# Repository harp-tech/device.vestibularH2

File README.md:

## Harp FastStepper

This repository contains the device metadata, firmware and high-level interface to the FastStepper device. Below are simple getting started instructions for maintainers to create a new device using the automatic code generators.

### Device metadata

#### Prerequisites

1. Install [Visual Studio Code](https://code.visualstudio.com/)
2. Install the [YAML](https://marketplace.visualstudio.com/items?itemName=redhat.vscode-yaml) extension.

The `device.yml` file in the root of the project contains the FastStepper device metadata. A complete specification of device registers, including any bit masks, group masks, and payload specs needs to be provided for code generation to work.

### Generating interface and firmware

#### Prerequisites

1. Install [`dotnet`](https://dotnet.microsoft.com/)
2. Install `dotnet-t4`
```
dotnet tool install -g dotnet-t4
```

The `Generators` folder contains all text templates and project files required to generate both the firmware headers and the interface for the FastStepper device. To run the text templating engine just build the project inside this folder.

```
cd Generators
dotnet build
```

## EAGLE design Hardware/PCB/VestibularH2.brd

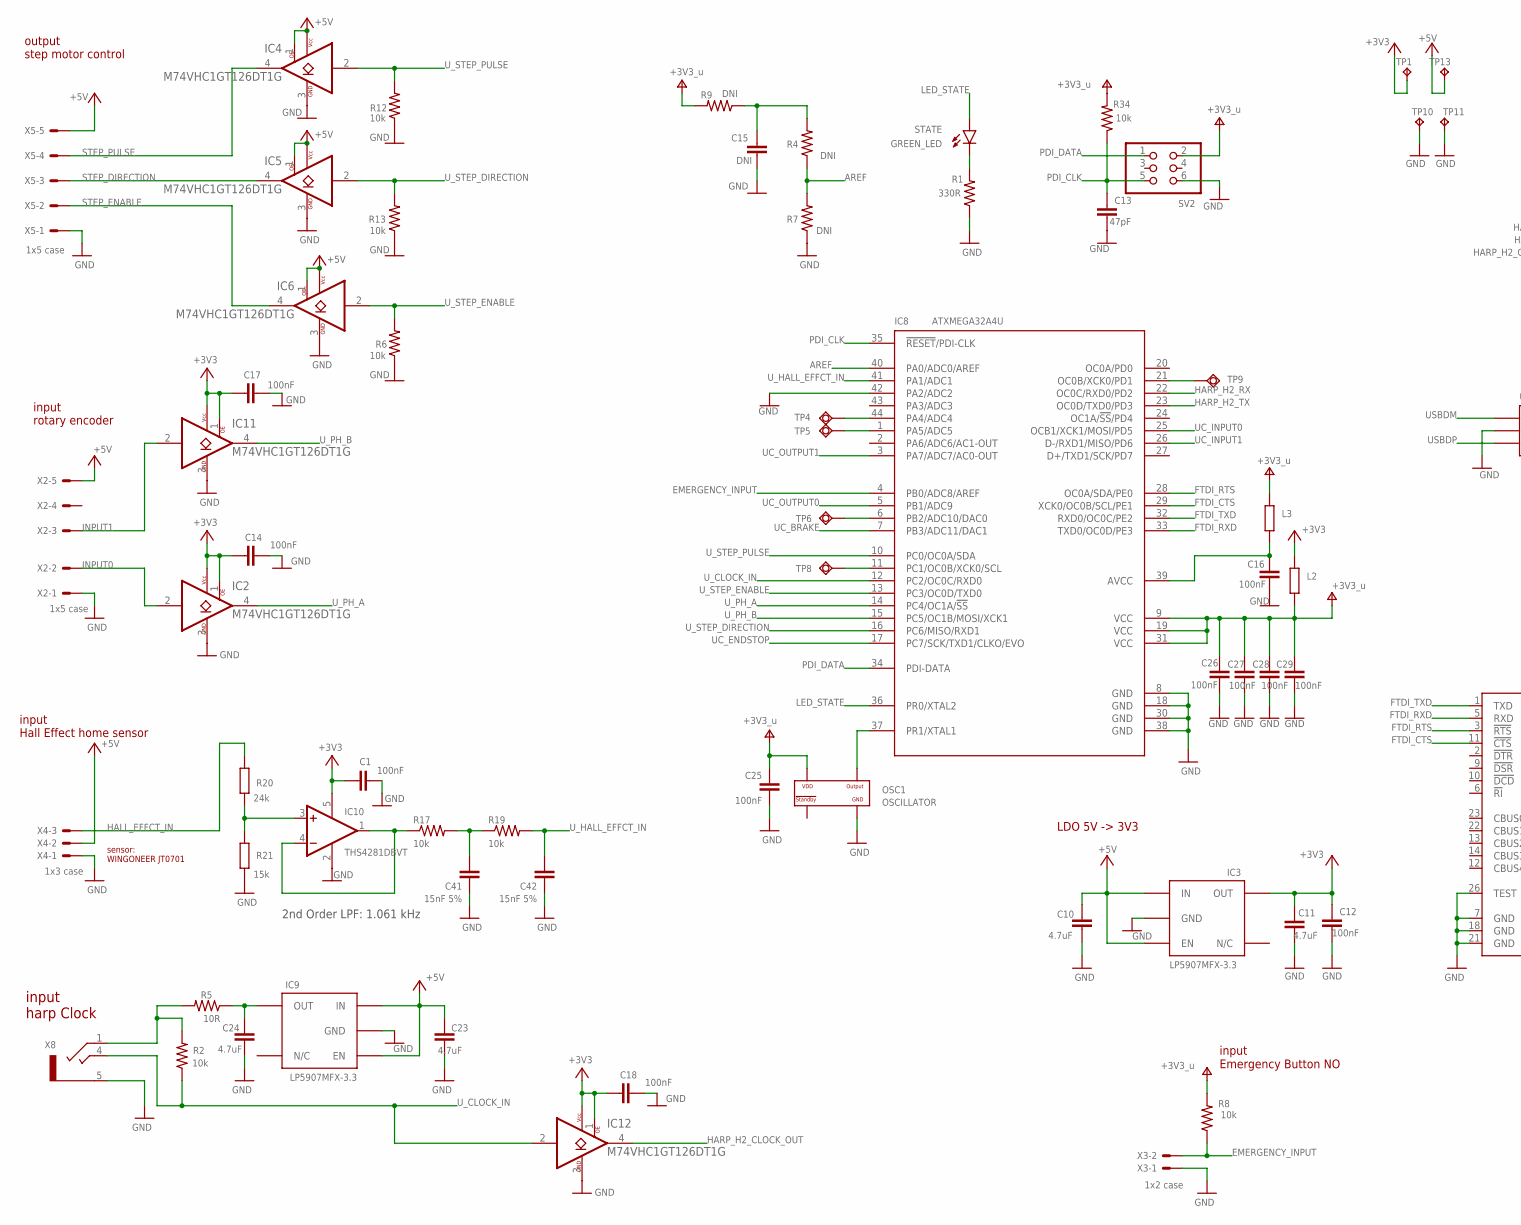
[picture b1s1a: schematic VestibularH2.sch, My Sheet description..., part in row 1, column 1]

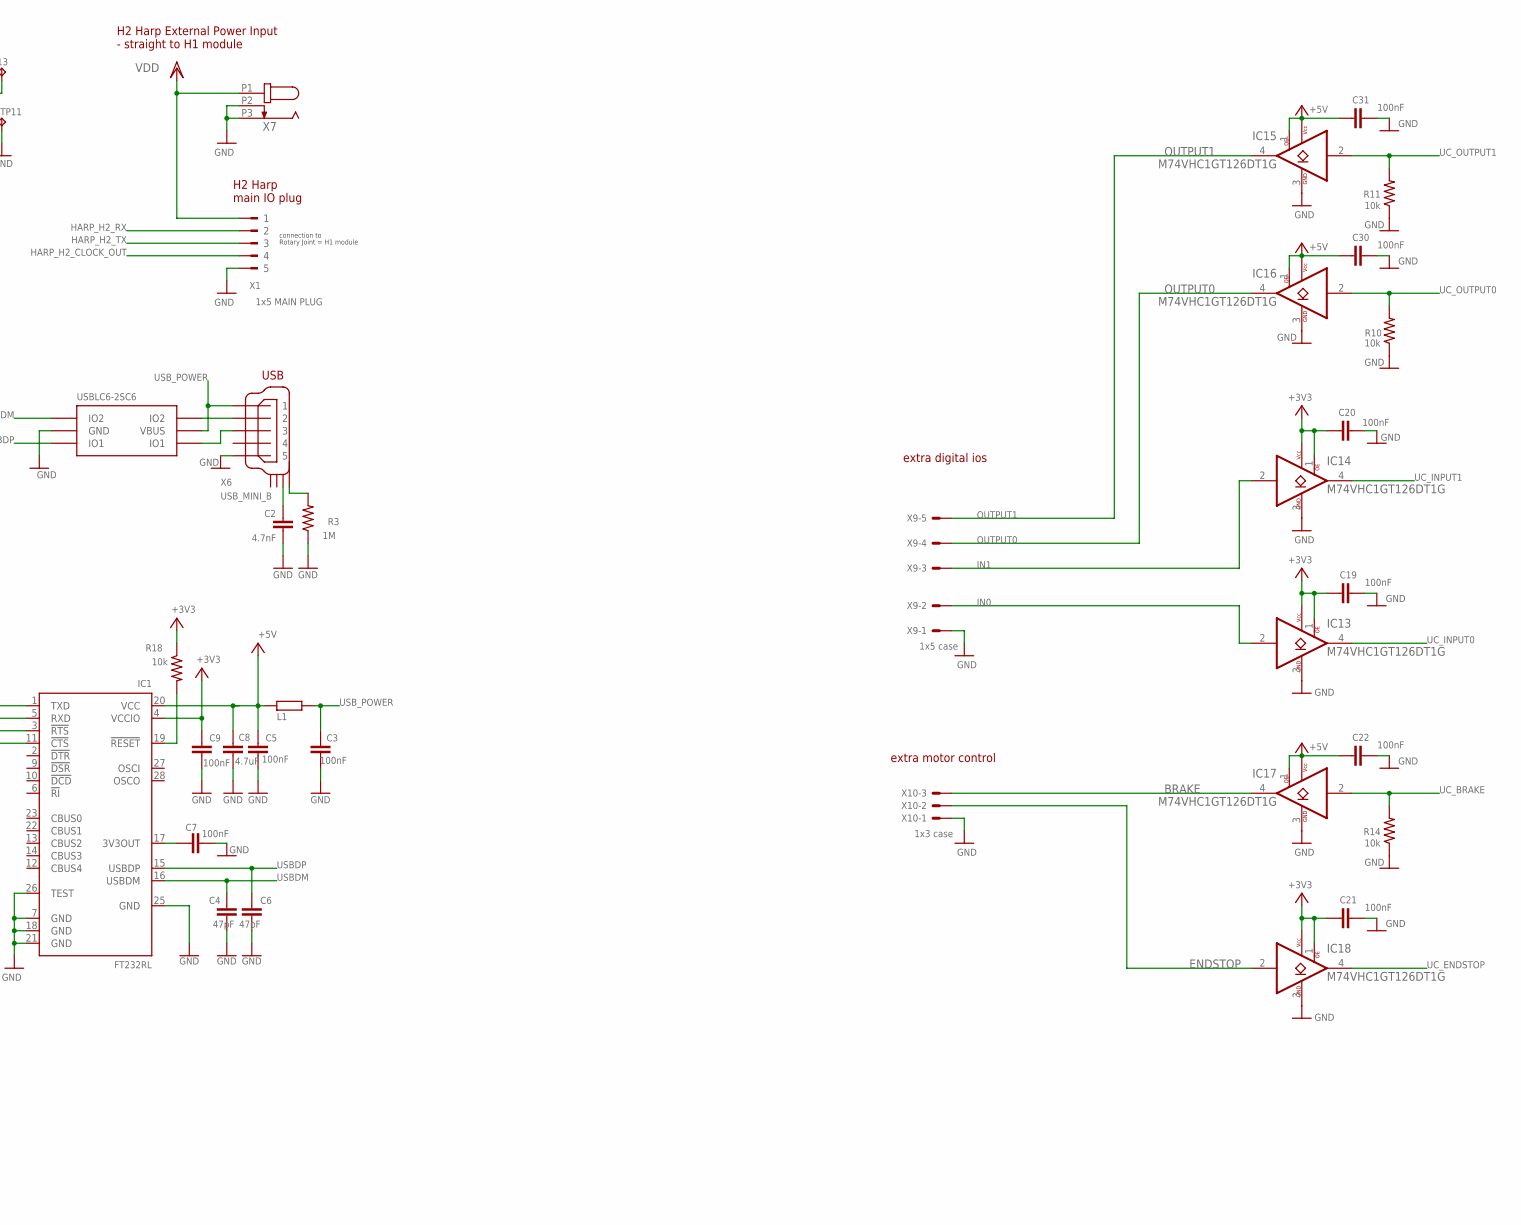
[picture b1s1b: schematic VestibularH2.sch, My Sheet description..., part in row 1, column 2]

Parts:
C1, C3, C5, C7, C9, C12, C14, C16, C17, C18, C19, C20, C21, C22, C25, C26, C27, C28, C29, C30, C31: 100nF; C0402K; MPN C1005X7R1H104K050BB
C2: 4.7nF; C0402K; MPN CC0402KRX7R8BB472
C4, C6, C13: 47pF; C0402K; MPN 04025A470JAT2A
C8, C10, C11, C23, C24: 4.7uF; C0603K; MPN C1608X6S1C475K080AC
C15: DNI; C0603K; MPN DNI
C41, C42: 15nF 5%; C0402K; MPN CGA2B3X7R1V153K050BB
IC1: FT232RL; SSOP28; MPN FT232RL
IC2, IC4, IC5, IC6, IC11, IC12, IC13, IC14, IC15, IC16, IC17, IC18: M74VHC1GT126DT1G; TSOP-5; MPN M74VHC1GT126DT1G; DIGIKEY_PN M74VHC1GT126DT1GOSDKR-ND
IC3, IC9: LP5907MFX-3.3; TSOT23-5; MPN LP5907MFX-3.3/NOPB
IC7: USBLC6-2SC6; SOT23-6L; MPN USBLC6-2SC6
IC8: ATXMEGA32A4U; TQFP44; MPN ATXMEGA32A4U-AUR
IC10: THS4281DBVT; SOT23-5; MPN THS4281DBVT
L1, L2, L3: 40R@100MHz; R0805; MPN MI0805K400R-10
OSC1: OSCILLATOR; OSCILLATOR_3.2X2.5; MPN DSC1001CI5-032.0000
R1: 330R; R0402; MPN RC0402FR-07330RL
R2, R6, R8, R10, R11, R12, R13, R14, R17, R18, R19, R34: 10k; R0402; MPN CRCW040210K0FKED
R3: 1M; R0402; MPN CRCW04021M00FKED
R4, R7, R9: DNI; R0402; MPN DNI
R5: 10R; R0402; MPN ERJ-PA2J100X
R20: 24k; R0402; MPN ERJ-2RKF2402X
R21: 15k; R0402; MPN ERJ-2RKF1502X
STATE: GREEN_LED; CHIP-LED0603; MPN LTST-C191KGKT
SV2: PINHD-2X3; 2X03; MPN 609-3210-ND
TP1, TP10, TP11, TP13: NO_COMPONENT; B1,27
TP4, TP5, TP6, TP8, TP9: NO_COMPONENT; TP11R
X1: 1x5 MAIN PLUG; 90G-5; MPN 20.155MH/5-E
X2, X5, X9: 1x5 case; 22-23-2051; MPN 282834-5
X3: 1x2 case; 22-23-2021; MPN 282834-2
X4, X10: 1x3 case; 22-23-2031; MPN 282834-3
X6: USB_MINI_B; 240-0002-1; MPN UX60-MB-5S8
X7: DC_JACK2.1MM; DC_POWER_INPUT_2.1MM; MPN 163-179PH-EX
X8: CLCK_JACK; 35RASMT2BHNTRX; MPN 35RASMT2BHNTRX

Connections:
+3V3: C1.1, C9.1, C11.1, C12.1, C14.1, C17.1, C18.1, C19.1, C20.1, C21.1, IC1.4 (VCCIO), IC2.1 (OE), IC2.5 (VCC), IC3.5 (OUT), IC10.5 (V+), IC11.1 (OE), IC11.5 (VCC), IC12.1 (OE), IC12.5 (VCC), IC13.1 (OE), IC13.5 (VCC), IC14.1 (OE), IC14.5 (VCC), IC18.1 (OE), IC18.5 (VCC), L2.2, R18.1, TP1.TP
+5V: C5.1, C8.1, C10.1, C22.1, C23.1, C30.1, C31.1, IC1.20 (VCC), IC3.1 (IN), IC3.3 (EN), IC4.1 (OE), IC4.5 (VCC), IC5.1 (OE), IC5.5 (VCC), IC6.1 (OE), IC6.5 (VCC), IC9.1 (IN), IC9.3 (EN), IC15.1 (OE), IC15.5 (VCC), IC16.1 (OE), IC16.5 (VCC), IC17.1 (OE), IC17.5 (VCC), L1.1, TP13.TP, X2.5, X4.2, X5.5
AREF: IC8.40 (PA0/ADC0/AREF), R4.1, R7.2
BRAKE: IC17.4 (Y), X10.3
EMERGENCY_INPUT: IC8.4 (PB0/ADC8/AREF), R8.1, X3.2
ENDSTOP: IC18.2 (A), X10.2
FTDI_CTS: IC1.11 (!CTS), IC8.29 (XCK0/OC0B/SCL/PE1)
FTDI_RTS: IC1.3 (!RTS), IC8.28 (OC0A/SDA/PE0)
FTDI_RXD: IC1.5 (RXD), IC8.33 (TXD0/OC0D/PE3)
FTDI_TXD: IC1.1 (TXD), IC8.32 (RXD0/OC0C/PE2)
GND: C1.2, C2.2, C3.2, C4.2, C5.2, C6.2, C7.2, C8.2, C9.2, C10.2, C11.2, C12.2, C13.2, C14.2, C15.2, C16.2, C17.2, C18.2, C19.2, C20.2, C21.2, C22.2, C23.2, C24.2, C25.2, C26.2, C27.2, C28.2, C29.2, C30.2, C31.2, C41.1, C42.1, IC1.7 (GND), IC1.18 (GND), IC1.21 (GND), IC1.25 (GND), IC1.26 (TEST), IC2.3 (GND), IC3.2 (GND), IC4.3 (GND), IC5.3 (GND), IC6.3 (GND), IC7.P$2 (GND), IC8.8 (GND), IC8.18 (GND), IC8.30 (GND), IC8.38 (GND), IC8.42 (PA2/ADC2), IC9.2 (GND), IC10.2 (V-), IC11.3 (GND), IC12.3 (GND), IC13.3 (GND), IC14.3 (GND), IC15.3 (GND), IC16.3 (GND), IC17.3 (GND), IC18.3 (GND), OSC1.P$2 (GND), R1.1, R3.1, R6.1, R7.1, R10.1, R11.1, R12.1, R13.1, R14.1, R21.1, SV2.6, TP10.TP, TP11.TP, X1.5, X2.1, X3.1, X4.1, X5.1, X6.P$5 (5), X7.P2 (2), X7.P3 (3), X8.5, X9.1, X10.1
HALL_EFFCT_IN: R20.2, X4.3
HARP_H2_CLOCK_OUT: IC12.4 (Y), X1.4
HARP_H2_RX: IC8.22 (OC0C/RXD0/PD2), X1.2
HARP_H2_TX: IC8.23 (OC0D/TXD0/PD3), X1.3
IN0: IC13.2 (A), X9.2
IN1: IC14.2 (A), X9.3
INPUT0: IC2.2 (A), X2.2
INPUT1: IC11.2 (A), X2.3
LED_STATE: IC8.36 (PR0/XTAL2), STATE.A
unnamed: R3.2, X6.SHIELD_4
unnamed: IC7.P$4 (IO2), X6.P$2 (2)
unnamed: IC7.P$6 (IO1), X6.P$3 (3)
unnamed: R1.2, STATE.C
unnamed: IC8.44 (PA4/ADC4), TP4.TP
unnamed: IC8.1 (PA5/ADC5), TP5.TP
unnamed: IC8.6 (PB2/ADC10/DAC0), TP6.TP
unnamed: C2.1, X6.SHIELD_3
unnamed: IC8.11 (PC1/OC0B/XCK0/SCL), TP8.TP
unnamed: IC8.21 (OC0B/XCK0/PD1), TP9.TP
unnamed: C7.1, IC1.17 (3V3OUT)
unnamed: C41.2, R17.2, R19.1
unnamed: C15.1, R4.2, R9.1
unnamed: C16.1, IC8.39 (AVCC), L3.1
unnamed: IC10.1 (OUT), IC10.4 (-IN), R17.1
unnamed: IC10.3 (+IN), R20.1, R21.2
unnamed: R2.2, R5.2, X8.1
unnamed: C24.1, IC9.5 (OUT), R5.1
unnamed: IC1.19 (!RESET), R18.2
OSC2: IC8.37 (PR1/XTAL1), OSC1.P$3 (OUTPUT)
OUTPUT0: IC16.4 (Y), X9.4
OUTPUT1: IC15.4 (Y), X9.5
PDI_CLK: C13.1, IC8.35 (!RESET!/PDI-CLK), R34.1, SV2.5
PDI_DATA: IC8.34 (PDI-DATA), SV2.1
STEP_DIRECTION: IC5.4 (Y), X5.3
STEP_ENABLE: IC6.4 (Y), X5.2
STEP_PULSE: IC4.4 (Y), X5.4
UC_BRAKE: IC8.7 (PB3/ADC11/DAC1), IC17.2 (A), R14.2
UC_ENDSTOP: IC8.17 (PC7/SCK/TXD1/CLKO/EVO), IC18.4 (Y)
UC_INPUT0: IC8.25 (OCB1/XCK1/MOSI/PD5), IC13.4 (Y)
UC_INPUT1: IC8.26 (D-/RXD1/MISO/PD6), IC14.4 (Y)
UC_OUTPUT0: IC8.5 (PB1/ADC9), IC16.2 (A), R10.2
UC_OUTPUT1: IC8.3 (PA7/ADC7/AC0-OUT), IC15.2 (A), R11.2
USBDM: C4.1, IC1.16 (USBDM), IC7.P$3 (IO2)
USBDP: C6.1, IC1.15 (USBDP), IC7.P$1 (IO1)
USB_POWER: C3.1, IC7.P$5 (VBUS), L1.2, X6.P$1 (1)
U_CLOCK_IN: IC8.12 (PC2/OC0C/RXD0), IC12.2 (A), R2.1, X8.4
U_HALL_EFFCT_IN: C42.2, IC8.41 (PA1/ADC1), R19.2
U_PH_A: IC2.4 (Y), IC8.14 (PC4/OC1A/!SS)
U_PH_B: IC8.15 (PC5/OC1B/MOSI/XCK1), IC11.4 (Y)
U_STEP_DIRECTION: IC5.2 (A), IC8.16 (PC6/MISO/RXD1), R13.2
U_STEP_ENABLE: IC6.2 (A), IC8.13 (PC3/OC0D/TXD0), R6.2
U_STEP_PULSE: IC4.2 (A), IC8.10 (PC0/OC0A/SDA), R12.2
V+: C25.1, C26.1, C27.1, C28.1, C29.1, IC8.9 (VCC), IC8.19 (VCC), IC8.31 (VCC), L2.1, L3.2, OSC1.P$4 (VDD), R8.2, R9.2, R34.2, SV2.2
VDD: X1.1, X7.P1 (1)

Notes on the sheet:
H2 Harp main IO plug
input rotary encoder
input Hall Effect home sensor
input harp Clock
output step motor control
input Emergency Button NO
USB
sensor: WINGONEER JT0701
H2 Harp External Power Input - straight to H1 module
connection to Rotary Joint = H1 module
2nd Order LPF: 1.061 kHz
LDO 5V -> 3V3
extra digital ios
extra motor control

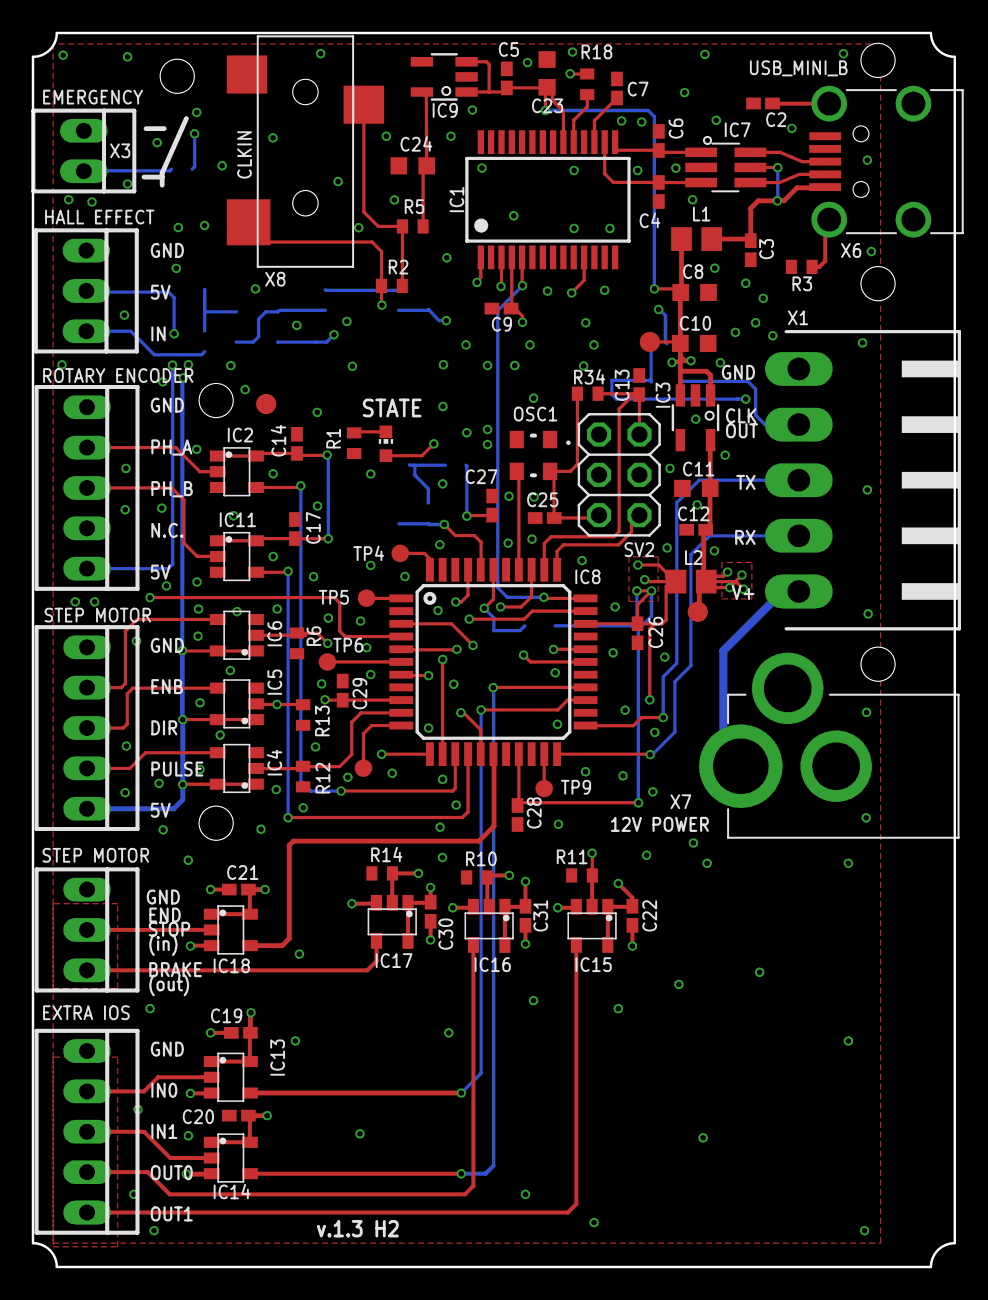
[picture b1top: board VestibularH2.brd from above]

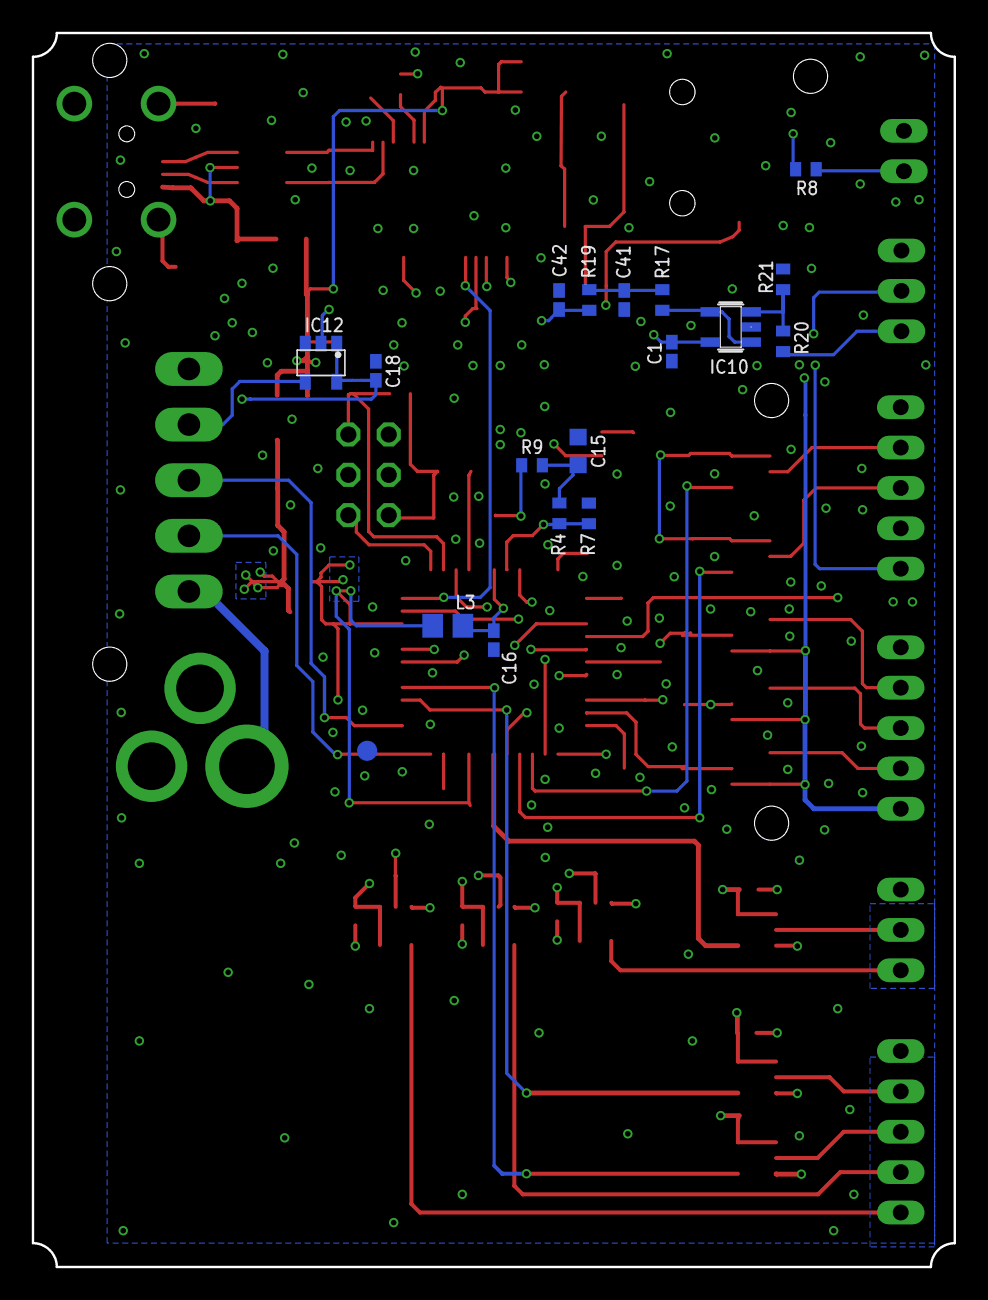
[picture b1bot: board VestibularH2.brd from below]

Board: 4 copper layers, 58.0 x 77.6 mm, 96 parts (18 on the bottom side), 65 nets.

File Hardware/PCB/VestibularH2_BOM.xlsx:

VestibularVR H2-module v1.1
.on board
Qty | Parts | Value | OEPS | MPN | Device | Package | Description
21 | C1, C3, C5, C7, C9, C12, C14, C16, C17, C18, C25, C26, C27, C19, C20, C21, C22,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 | 100nF | OEPS010004 | C1005X7R1H104K050BB | C-EUC0402K | C0402K | CAPACITOR, European symbol
1 | R5 | 10R | OEPS020041 | ERJ-PA2J100X | R-US_R0402 | R0402 | RESISTOR, American symbol
12 | R2, R6, R8, R10, R11, R12, R13, R14, R17, R18, R19, R34 | 10k | OEPS020030 | CRCW040210K0FKED | R-US_R0402 | R0402 | RESISTOR, American symbol
1 | R21 | 15k | OEPS020015 | ERJ-2RKF1502X | R-EU_R0402 | R0402 | RESISTOR, European symbol
2 | C41, C42 | 15nF 5% | OEPS010023 | CGA2B3X7R1V153K050BB | C-EUC0402K | C0402K | CAPACITOR, European symbol
1 | R3 | 1M | OEPS020026 | CRCW04021M00FKED | R-US_R0402 | R0402 | RESISTOR, American symbol
1 | X3 | 1x2 case | OEPS070020 | 282834-2 | 22-23-2021 | 22-23-2021 | .100 (2.54mm) Center Header - 2 Pin"
2 | X4, X10 | 1x3 case | OEPS070035 | 282834-3 | 22-23-2031 | 22-23-2031 | .100 (2.54mm) Center Header - 3 Pin"
1 | X1 | 1x5 MAIN PLUG | OEPS070037 | 20.155MH/5-E | 90G-5 | 90G-5 | WEIDMUELLER CLAMP CONNECTOR
3 | X2, X5, X9 | 1x5 case | OEPS070041 | 282834-5 | 22-23-2051 | 22-23-2051 | .100 (2.54mm) Center Header - 5 Pin"
1 | R20 | 24k | OEPS020048 | ERJ-2RKF2402X | R-EU_R0402 | R0402 | RESISTOR, European symbol
1 | R1 | 330R | OEPS020037 | RC0402FR-07330RL | R-US_R0402 | R0402 | RESISTOR, American symbol
1 | C2 | 4.7nF | OEPS010001 | CC0402KRX7R8BB472 | C-EUC0402K | C0402K | CAPACITOR, European symbol
5 | C8, C10, C11, C23, C24 | 4.7uF | OEPS010018 | C1608X6S1C475K080AC | C-EUC0603K | C0603K | CAPACITOR, European symbol
3 | L1, L2, L3 | 40R@100MHz | OEPS040003 | MI0805K400R-10 | R-EU_R0805 | R0805 | RESISTOR, European symbol
3 | C4, C6, C13 | 47pF | OEPS010011 | 04025A470JAT2A | C-EUC0402K | C0402K | CAPACITOR, European symbol
1 | IC8 | ATXMEGA32A4U | OEPS080012 | ATXMEGA32A4U-AUR | XMEGA-A4_AT-XMEGA-XXA4-AUTQFP44 | TQFP44 | ATxMega a4 Serie
1 | X8 | CLCK_JACK | OEPS070025 | 35RASMT2BHNTRX | STEREO_JACK | 35RASMT2BHNTRX | CONN JACK STEREO 3.5MM SMD R/A
1 | X7 | DC_JACK2.1MM | OEPS070026 | 163-179PH-EX | DC_JACK2.1MM | DC_POWER_INPUT_2.1MM | DC Power Connectors PCB 2.1MM
1 | C15 | DNI | DNI | DNI | C-EUC0603K | C0603K | CAPACITOR, European symbol
3 | R4, R7, R9 | DNI | DNI | DNI | R-US_R0402 | R0402 | RESISTOR, American symbol
1 | IC1 | FT232RL | OEPS080013 | FT232RL | FT232RL | SSOP28 | UART/FIFO IC
1 | STATE | GREEN_LED | OEPS030005 | LTST-C191KGKT | LEDCHIP-LED0603 | CHIP-LED0603
2 | IC3, IC9 | LP5907MFX-3.3 | OEPS080016 | LP5907MFX-3.3/NOPB | TLV700XX | TSOT23-5 | C REG LINEAR 3.3V 200MA SOT23-5
12 | IC2, IC4, IC5, IC6, IC11, IC12, IC13, IC14, IC15, C16, IC17, IC18 | M74VHC1GT126DT1G | OEPS080017 | M74VHC1GT126DT1G | M74VHC1GT126DT1G | TSOP-5
1 | OSC1 | OSCILLATOR | OEPS080018 | DSC1001CI5-032.0000 | OSCILLATOR | OSCILLATOR_3.2X2.5 | XTAL OSC TCXO 32.0000MHZ HCMOS
1 | SV2 | PINHD-2X3 | OEPS070015 | 609-3210-ND | PINHD-2X3 | 2X03 | PIN HEADER
1 | IC10 | THS4281DBVT | OEPS080038 | THS4281DBVT | OPA365 | SOT23-5
1 | IC7 | USBLC6-2SC6 | OEPS030010 | USBLC6-2SC6 | USBLC6-2SC6 | SOT23-6L | TVS DIODE 5.25VWM 17VC SOT23-6
1 | X6 | USB_MINI_B | OEPS070021 | UX60-MB-5S8 | USB_MINI_B | 240-0002-1 | CONN RCPT USB2.0 MINI B SMD R/A
.off board
N.A.

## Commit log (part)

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2022-11-22 BOMs & start Harp Motor device H2-module v1.0
    . almost final BOMs versions for VestibularVR H1-module v1.0 & Lick Sensor module v1.0
    . start of new project Harp Motor device H2-module v1.0
2022-11-23 Harp Motor device H2 - design
    still first steps on Eagle Harp Motor device H2 design
2022-12-05 VestibularVR H1BOM updates & Lick Sensor step on
    - VestibularVR H1
    . component ref updated
    . BOM file updated
    - Lick Sensor module v1.0
    . still only on schematic design
2022-12-07 Harp Motor device H2-module v1.0 - Schematic step on
    Harp Motor device H2-module v1.0 - Schematic step on
2022-12-09 Harp Motor device H2-module v1.0 - design proceeding
    Harp Motor device H2-module v1.0 - design proceeding
2022-12-13 Harp Motor device H2-module v1.0 - 1st 'finished' version
    Harp Motor device H2-module v1.0 - 1st 'finished' version
    - missing:
    . some schm & pcb review with Filipe
    . components order codes & BOM
2022-12-14 Harp Motor device H2-module v1.0; commit after revision
    Harp Motor device H2-module v1.0:
    - commit after revisions made with Filipe @Dezember 14th 2022
    - missing components OEPS code & BOM
2022-12-16 Harp Motor device H2-module v1.0 - last revision with Filipe
    - extra R0 on some stages
    - IO headers - GND pin was on wrong end
    - rebuild user-friend labelling
    - still missing OEPS components code & BOM
2022-12-16 Harp Motor device H2-module v1.0 - silk screen corrections
    Harp Motor device H2-module v1.0
    - silk screen positions corrections
    - still missing OEPS parts codes & BOM
2022-12-19 Harp Motor device H2-module v1.0 - final changes
    Harp Motor device H2-module v1.0 - final PCB changes
    - labels sizes & positions modified
    - removed clock conn from micro to main plug; added direct buffer from clock_in to main harp plug;
    - corrected Harp_Tx & Harp_Rx pins
    - still missing BOM & OEPS components codes
2022-12-20 Harp Motor device H2-module v1.0 - BOM not finished
    Harp Motor device H2-module v1.0
    - BOM committed; not yet finished
2022-12-22 Harp Motor device H2-module v1.0 - BOM updated
    Harp Motor device H2-module v1.0 - BOM updated
    - still missing component's codes
2023-01-10 Harp Motor device H2-module v1.0 BOM updated
    Harp Motor device H2-module v1.0 BOM updated
    - OEPS & MPN components code changed
    - new BOM generated
2023-01-11 Harp Motor device H2-module v1.0 - BOM updated
    Harp Motor device H2-module v1.0 - BOM updated
    - new component codes on schematic
    - new BOM generated
2023-01-12 Harp Motor device H2-module v1.0 - BOM updated
    Harp Motor device H2-module v1.0 - BOM updated
    - THS4281DBVT OPES code updated: OEPS080038
    - schematic updated
    - BOM updated
2023-01-15 Reorganize repository to match standard template
2023-03-13 Added the first firmware files.
2023-03-13 Added a Bonsai workflow to help development.
2023-03-13 Added equation to calculate voltage.
2023-03-13 Deleted unnecessary comments.
2023-03-13 Cancel pulse drive when the user disables the motor.
2023-03-13 Disable medium and high level interrupts.
    Disable medium and high level interrupts to transform the motor global variables into global atomic variables.
2023-03-13 Raised firmware version to 0.3.
2023-03-14 Make register Control non-volatile.
2023-03-15 Created new register called Moving.
    Took the opportunity to correct a typo.
2023-03-15 Removed unnecessary information.
2023-03-15 Send event when all steps where dispatched.
2023-03-15 Implemented protection to stop motor.
    Implemented protection to stop motor when the device goes to Standby Mode.
2023-03-15 Made register Moving readable.
2023-04-26 Corrected WHO_AM_I
2023-04-26 Increased fw version to 0.4
2023-04-26 Renamed project
2023-05-16 Decreased step interval to increase motor speed.
2023-05-16 Added new register IMMEDIATE_PULSES on address 42.
2023-05-16 Implemented the funtionality.
2023-05-16 Minor corrections.
2023-08-31 Raised firmware version.
2023-09-01 Replaced harp core 1.12 with 1.13.
2023-09-05 Replaced files with PCB version 1.1.
2023-09-05 Replaced BOM to match PCB version 1.1.
2023-11-27 Add first iteration of auto generated interface
2023-11-27 Update device schema
2023-11-27 Update generator package and regenerate interface
2023-11-27 Add interface license file
2024-03-20 Fix top silk.
    Fixed label of Hall effect' connector.
2024-06-28 Implemented serial reception.
2024-06-28 Implemented serial decode.
2024-06-28 Added motion.
2024-11-18 Created the schematic with new ios.
2024-11-22 Finalized the layout.
2025-01-24 Rename VestibularH2 to FastStepper
2025-01-24 Add missing licenses for all design components
2025-01-24 Remove obsolete test workflows
2025-01-24 Add license for documentation assets
2025-01-24 Update package metadata
2025-01-24 Tentative update to device WhoAmI
2025-02-18 added Heartbeat (reg. 8) to device.yml
